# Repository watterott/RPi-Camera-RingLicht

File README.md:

# RPi-Camera-RingLicht
Camera Light for Raspberry Pi camera v1 and v2.

* 12x WS2812 RGB-LED with built-in controller with serial interface
* Open-Source and released under the [Creative Commons Attribution Share-Alike License](https://creativecommons.org/licenses/by-sa/4.0/).
* **[Documentation on learn.watterott.com](https://learn.watterott.com)**

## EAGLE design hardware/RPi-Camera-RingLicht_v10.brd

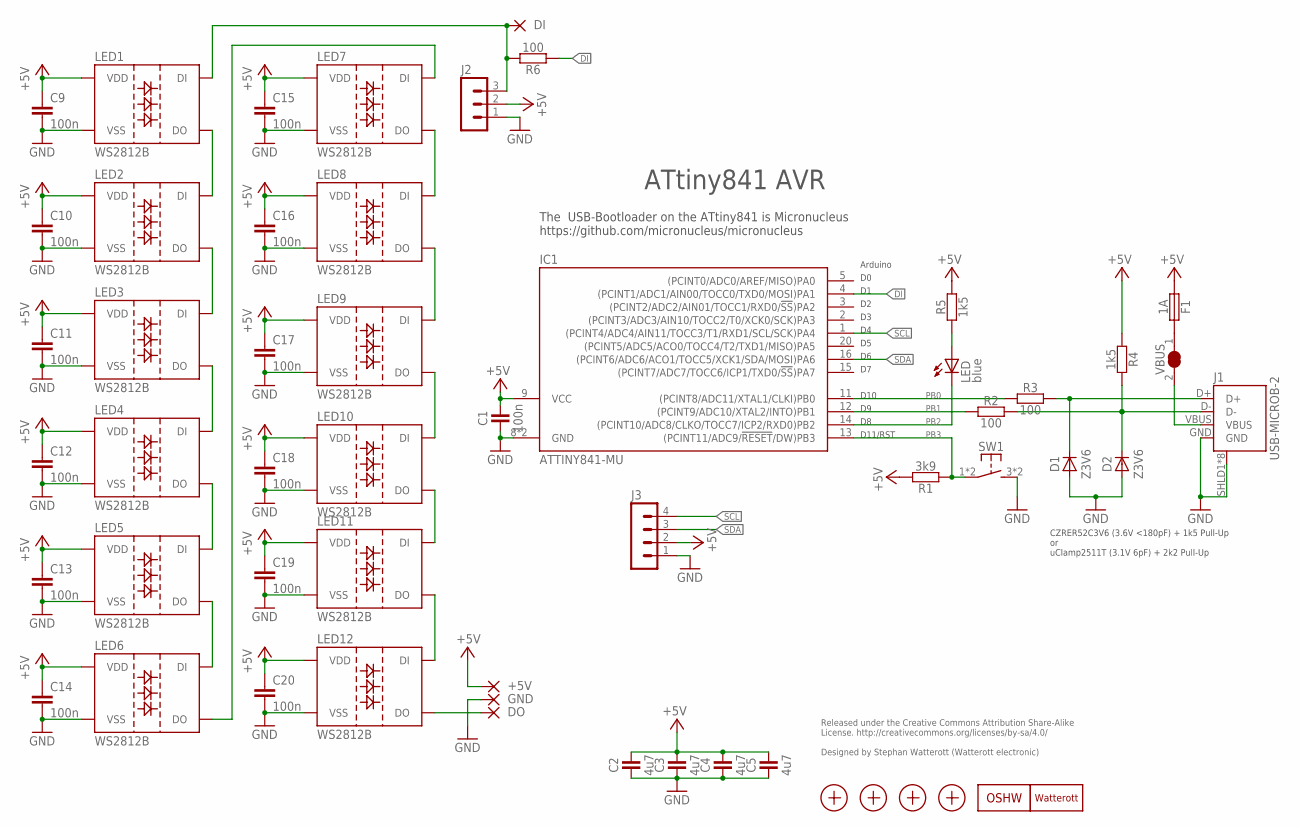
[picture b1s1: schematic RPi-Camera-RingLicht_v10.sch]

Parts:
+5V: SMD2; SMD1,27-2,54
C1: 100n; C0402
C2, C3, C4, C5: 4u7; C0402
C9, C10, C11, C12, C13, C14, C15, C16, C17, C18, C19, C20: 100n; C0402K
D1, D2: Z3V6; SOD882
DI: SMD2; SMD1,27-2,54
DO: SMD2; SMD1,27-2,54
F1: 1A; C0805
GND: SMD2; SMD1,27-2,54
IC1: ATTINY841-MU; QFN20-PAD
J1: USB-MICROB-2; USB-MICROB-10118194
J2: JST3-S3B-PH-SM4-TB; JST_S3B-PH-SM4-TB
J3: JST4-S4B-PH-SM4-TB; JST_S4B-PH-SM4-TB
LED: blue; C0603
LED1, LED2, LED3, LED4, LED5, LED6, LED7, LED8, LED9, LED10, LED11, LED12: WS2812B
LOGO1: LOGO-S_PLACE_M; SPARK_TPLACE_M
LOGO2: OSHW_LOGOX0070; OSHW_6X70
R1: 3k9; C0402
R2, R3, R6: 100; C0402
R4, R5: 1k5; C0402
SW1: SW-TACTILE-PTS840P; PTS840P
VBUS: JUMPER2-0603-NC; JUMPER2-0603_NC
X1, X2, X3, X4: PASSER-07; PASSER_07MM

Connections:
+5V: +5V.1, C1.2, C2.2, C3.2, C4.2, C5.2, C9.1, C10.1, C11.1, C12.1, C13.1, C14.1, C15.1, C16.1, C17.1, C18.1, C19.1, C20.1, F1.1, IC1.9 (VCC), J2.2, J3.2, LED1.1 (VDD), LED2.1 (VDD), LED3.1 (VDD), LED4.1 (VDD), LED5.1 (VDD), LED6.1 (VDD), LED7.1 (VDD), LED8.1 (VDD), LED9.1 (VDD), LED10.1 (VDD), LED11.1 (VDD), LED12.1 (VDD), R1.2, R4.1, R5.2
DI: IC1.4 ((PCINT1/ADC1/AIN00/TOCC0/TXD0/MOSI)PA1), R6.1
D_N: D2.C, J1.D-, R2.2, R4.2
D_P: D1.C, J1.D+, R3.2
GND: C1.1, C2.1, C3.1, C4.1, C5.1, C9.2, C10.2, C11.2, C12.2, C13.2, C14.2, C15.2, C16.2, C17.2, C18.2, C19.2, C20.2, D1.A, D2.A, GND.1, IC1.8 (GND), IC1.TP (GND), J1.GND, J1.SHLD1 (SHIELD), J1.SHLD2 (SHIELD), J1.SHLD3 (SHIELD), J1.SHLD4 (SHIELD), J1.SHLD5 (SHIELD), J1.SHLD6 (SHIELD), J1.SHLD7 (SHIELD), J1.SHLD8 (SHIELD), J2.1, J3.1, LED1.3 (VSS), LED2.3 (VSS), LED3.3 (VSS), LED4.3 (VSS), LED5.3 (VSS), LED6.3 (VSS), LED7.3 (VSS), LED8.3 (VSS), LED9.3 (VSS), LED10.3 (VSS), LED11.3 (VSS), LED12.3 (VSS), SW1.3 (S1), SW1.4 (S1)
LED+: LED.A, R5.1
unnamed: F1.2, VBUS.1
unnamed: LED1.2 (DO), LED2.4 (DI)
unnamed: LED2.2 (DO), LED3.4 (DI)
unnamed: LED3.2 (DO), LED4.4 (DI)
unnamed: LED4.2 (DO), LED5.4 (DI)
unnamed: LED5.2 (DO), LED6.4 (DI)
unnamed: LED6.2 (DO), LED7.4 (DI)
unnamed: LED7.2 (DO), LED8.4 (DI)
unnamed: LED9.2 (DO), LED10.4 (DI)
unnamed: LED10.2 (DO), LED11.4 (DI)
unnamed: LED11.2 (DO), LED12.4 (DI)
unnamed: LED8.2 (DO), LED9.4 (DI)
unnamed: DI.1, J2.3, LED1.4 (DI), R6.2
unnamed: DO.1, LED12.2 (DO)
PB0: IC1.11 ((PCINT8/ADC11/XTAL1/CLKI)PB0), R3.1
PB1: IC1.12 ((PCINT9/ADC10/XTAL2/INTO)PB1), R2.1
PB2: IC1.14 ((PCINT10/ADC8/CLKO/TOCC7/ICP2/RXD0)PB2), LED.C
PB3: IC1.13 ((PCINT11/ADC9/!RESET!/DW)PB3), R1.1, SW1.1, SW1.2 (P1)
SCL: IC1.1 ((PCINT4/ADC4/AIN11/TOCC3/T1/RXD1/SCL/SC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), J3.4
SDA: IC1.16 ((PCINT6/ADC6/ACO1/TOCC5/XCK1/SDA/MOSI)P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), J3.3
VBUS1: J1.VBUS, VBUS.2

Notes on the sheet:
Released under the Creative Commons Attribution Share-Alike License. http://creativecommons.org/licenses/by-sa/4.0/ Designed by Stephan Watterott (Watterott electronic)
The USB-Bootloader on the ATtiny841 is Micronucleus https://github.com/micronucleus/micronucleus
CZRER52C3V6 (3.6V <180pF) + 1k5 Pull-Up or uClamp2511T (3.1V 6pF) + 2k2 Pull-Up
ATtiny841 AVR
Arduino
D10
D11/RST

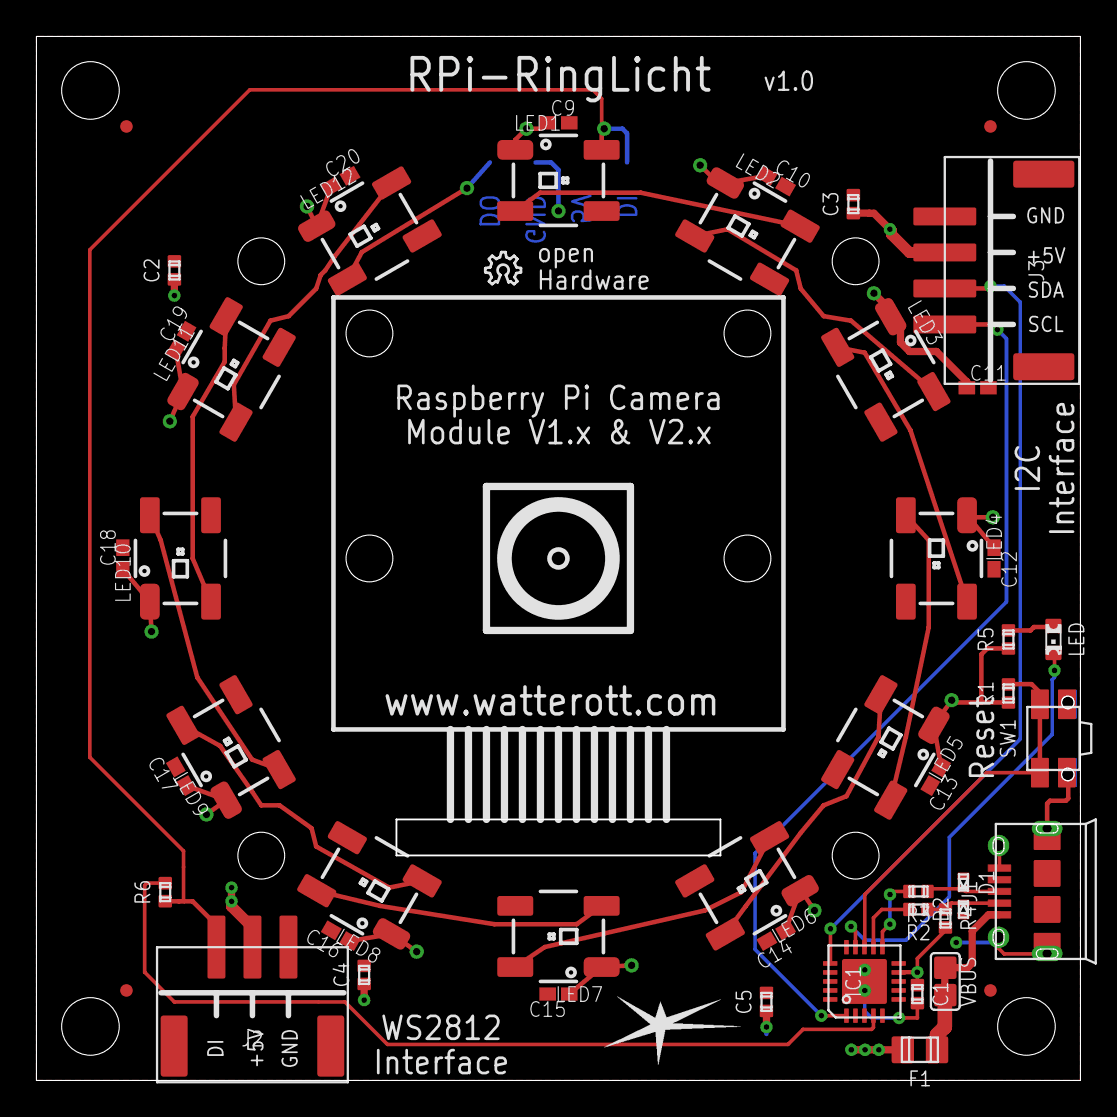
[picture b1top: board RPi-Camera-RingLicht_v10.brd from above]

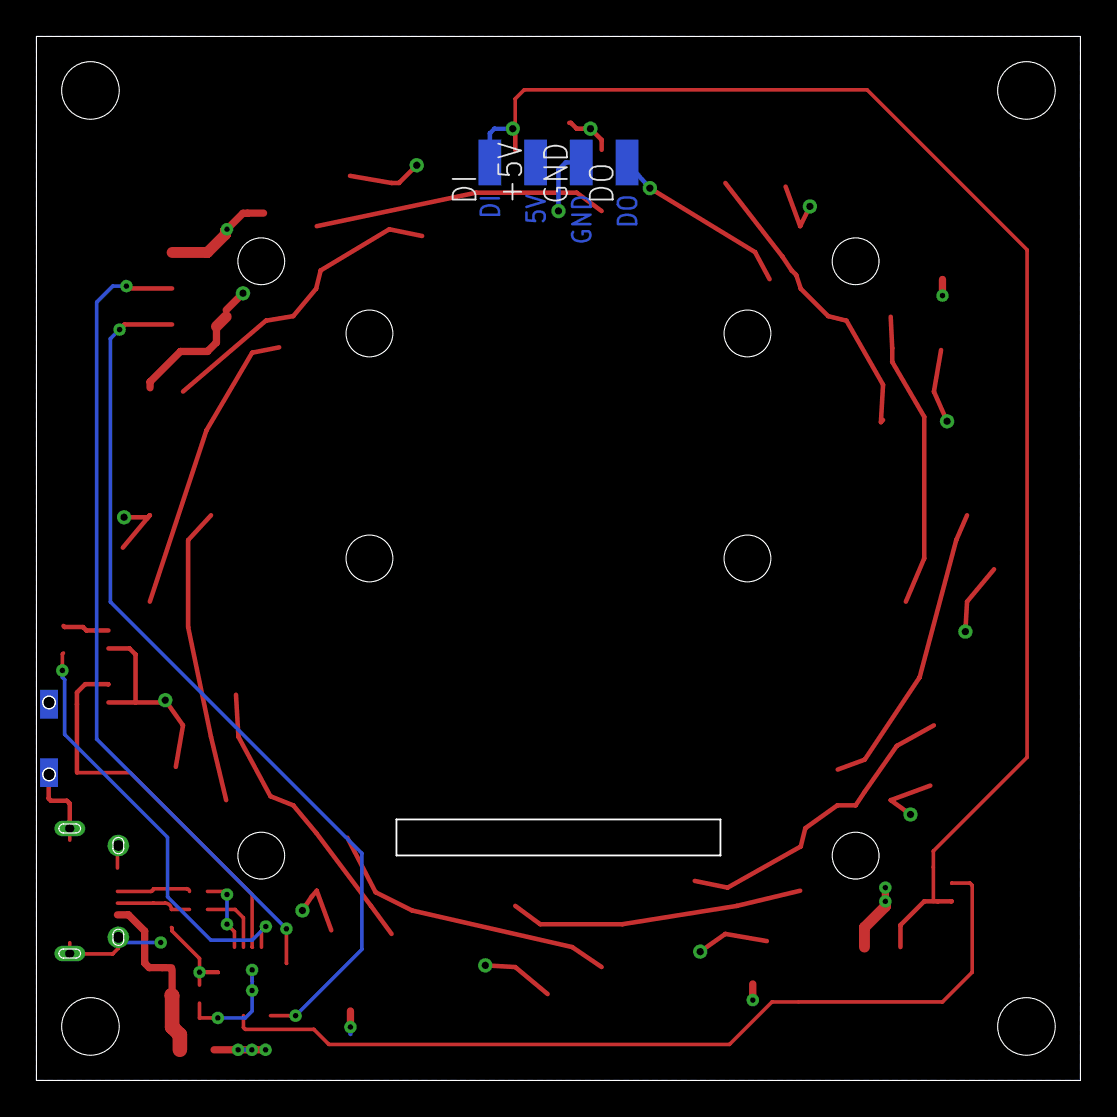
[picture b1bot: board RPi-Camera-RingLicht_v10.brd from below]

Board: 2 copper layers, 57.9 x 57.9 mm, 55 parts (4 on the bottom side), 27 nets.
